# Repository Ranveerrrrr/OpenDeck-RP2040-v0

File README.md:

# OpenDeck-RP2040-v0

OpenDeck-RP2040-v0 is an early hardware prototype of a DIY macro pad inspired by the Elgato Stream Deck.  
This project represents my **first-ever hardware design**, created as a learning experiment using KiCad with no prior background in electronics or PCB design.

---

## Project Overview

The goal of this project was to explore the fundamentals of hardware design, including schematic capture, PCB layout, and basic I/O expansion using a microcontroller.

At the time of creation(2025), I had no formal knowledge of electronics. I downloaded KiCad, had the concept of a Stream Deck–style device in mind, and designed this board through experimentation and self-learning. The result is a functional concept design rather than a finished or production-ready product.

---

## Hardware Summary

- Microcontroller: Seeed XIAO RP2040  
- Button input expansion: PCF8574 (I²C I/O expander)  
- LED output expansion: 74HC595 (shift register)  
- Inputs: 9 tactile push buttons  
- Outputs: 9 individual LED indicators  
- Interface: USB (via RP2040)

---

## Design Files & Visuals

### Schematic

### PCB Layout

### 3D Render

---

## Repository Contents

- KiCad schematic and PCB files
- Custom symbols, footprints, and 3D models
- Project documentation
- No finalized firmware
- No enclosure or mechanical design

---

## Project Status

**Status: Incomplete / Prototype (v0)**

- Firmware was never completed
- Hardware was not extensively tested
- Design was not revised after the initial version
- This version is considered **frozen**

I may revisit this concept in the future. Any continued development or improvements will be done in a **separate repository (v2)**.  
This repository will remain unchanged as an archive of the original prototype.

---

## Motivation

This project was inspired by the Elgato Stream Deck.  
It was created purely as a learning exercise to understand how an idea could be translated into a real PCB using KiCad, without prior experience in hardware design.

The intent was exploration, not perfection.

---

## Disclaimer

This design is experimental and provided for reference purposes only.  
It is not guaranteed to function as intended and is not suitable for production use.

---

## License

This project is licensed under the MIT License.

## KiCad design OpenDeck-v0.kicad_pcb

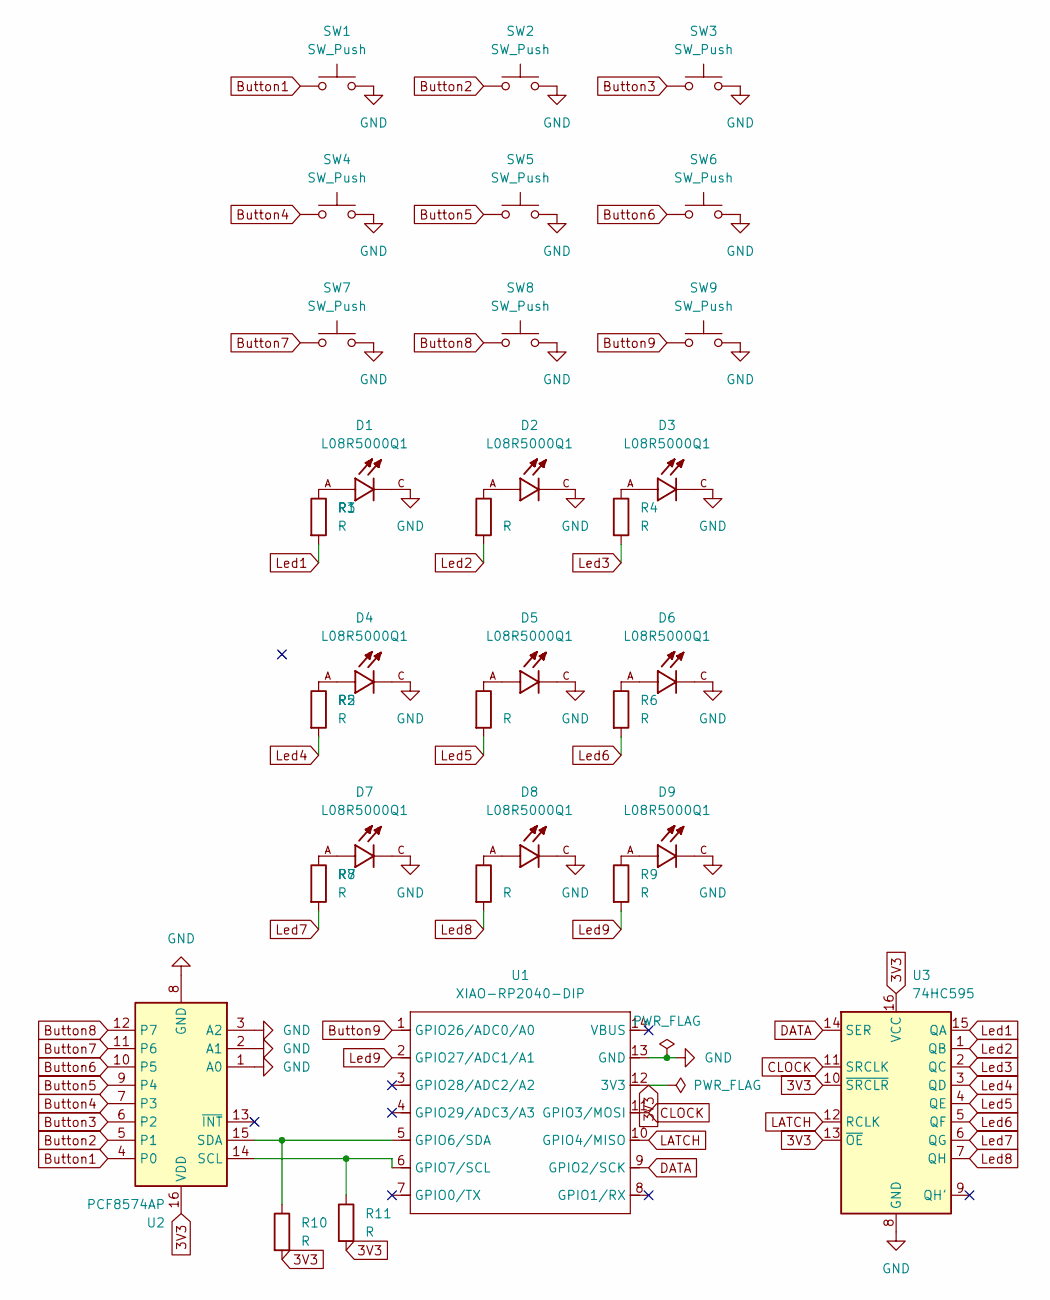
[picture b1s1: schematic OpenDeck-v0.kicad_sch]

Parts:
D1, D2, D3, D4, D5, D6, D7, D8, D9: L08R5000Q1; LEDRD254W57D500H1070; PARTREV NA
R1, R2, R3, R4, R5, R6, R7, R8, R9, R10, R11: R; R_Axial_DIN0204_L3.6mm_D1.6mm_P5.08mm_Horizontal
SW1, SW2, SW3, SW4, SW5, SW6, SW7, SW8, SW9: SW_Push; SW_PUSH_6mm_H9.5mm
U1: XIAO-RP2040-DIP
U2: PCF8574AP; DIP-16_W7.62mm
U3: 74HC595; DIP-16_W7.62mm

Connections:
3V3: R10.2, R11.2, U1.12 (3V3), U2.16 (VDD), U3.10 (~SRCLR), U3.13 (~OE), U3.16 (VCC)
Button1: SW1.1, U2.4 (P0)
Button2: SW2.1, U2.5 (P1)
Button3: SW3.1, U2.6 (P2)
Button4: SW4.1, U2.7 (P3)
Button5: SW5.1, U2.9 (P4)
Button6: SW6.1, U2.10 (P5)
Button7: SW7.1, U2.11 (P6)
Button8: SW8.1, U2.12 (P7)
Button9: SW9.1, U1.1 (GPIO26/ADC0/A0)
CLOCK: U1.11 (GPIO3/MOSI), U3.11 (SRCLK)
DATA: U1.9 (GPIO2/SCK), U3.14 (SER)
GND: D1.C, D2.C, D3.C, D4.C, D5.C, D6.C, D7.C, D8.C, D9.C, SW1.2, SW2.2, SW3.2, SW4.2, SW5.2, SW6.2, SW7.2, SW8.2, SW9.2, U1.13 (GND), U2.1 (A0), U2.2 (A1), U2.3 (A2), U2.8 (GND), U3.8 (GND)
LATCH: U1.10 (GPIO4/MISO), U3.12 (RCLK)
Led1: R1.2, U3.15 (QA)
Led2: R3.2, U3.1 (QB)
Led3: R4.2, U3.2 (QC)
Led4: R2.2, U3.3 (QD)
Led5: R5.2, U3.4 (QE)
Led6: R6.2, U3.5 (QF)
Led7: R7.2, U3.6 (QG)
Led8: R8.2, U3.7 (QH)
Led9: R9.2, U1.2 (GPIO27/ADC1/A1)
unnamed: D1.A, R1.1
unnamed: D2.A, R3.1
unnamed: D3.A, R4.1
unnamed: D4.A, R2.1
unnamed: D5.A, R5.1
unnamed: D6.A, R6.1
unnamed: D7.A, R7.1
unnamed: D8.A, R8.1
unnamed: D9.A, R9.1
unnamed: R10.1, U1.5 (GPIO6/SDA), U2.15 (SDA)
unnamed: R11.1, U1.6 (GPIO7/SCL), U2.14 (SCL)

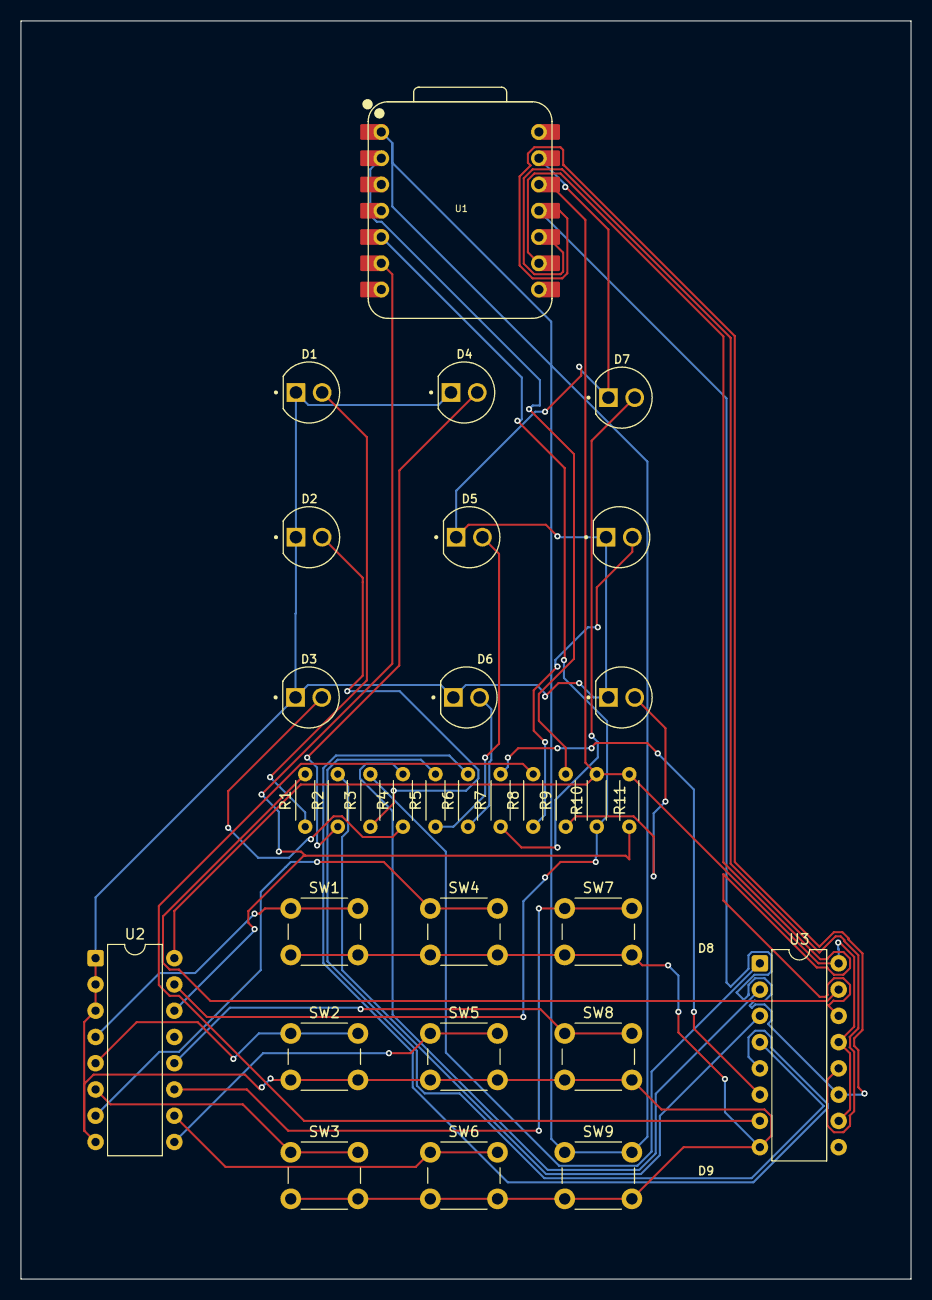
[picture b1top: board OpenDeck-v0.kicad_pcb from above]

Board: 2 copper layers, 86.1 x 121.7 mm, 32 parts (0 on the bottom side), 34 nets.

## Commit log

2026-03-03 Initial commit: OpenDeck RP2040 macro pad prototype (v0)
2026-03-03 Ignore KiCad autosave files and update board files
2026-03-03 Organized Files
2026-03-03 Readme Update

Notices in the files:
README.md:
License: MIT
